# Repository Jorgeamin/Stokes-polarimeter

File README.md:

# Stokes-polarimeter
Supplement documents for article "Homemade open-source full-Stokes polarimeter based on division of amplitude"

* [python](python): This folder contains python scripts for user interface.\
    main application file **stokes_polarimeter.py**\
     -line 517:  ### Here your put the result of the calibration of the photodiodes ###\
     -line 526:  ### Here your put the result of the calibration to obtain the Stokes parameters ###
  
* [firmware](firmware): This folder contains MPLAB Harmony 3 firmware that should be installed in an ATSAML21E16B\
    file **main.c**\
	-line 97:  /// Here your put the result of the calibration of the photodiodes ///\
	-line 106: /// Here your put the result of the calibration to obtain the Stokes parameters ///
	
* [pcb](pcb): This folder contains the Autodesk Eagle electronic design files.
* [3d](3d): This folder contains the 3D Autodesk Inventor, STEP and STL files.
* [pdf](pdf): This folder contains the electronic diagrams and the 3D assembly in PDF format.

-this repository uses submodules

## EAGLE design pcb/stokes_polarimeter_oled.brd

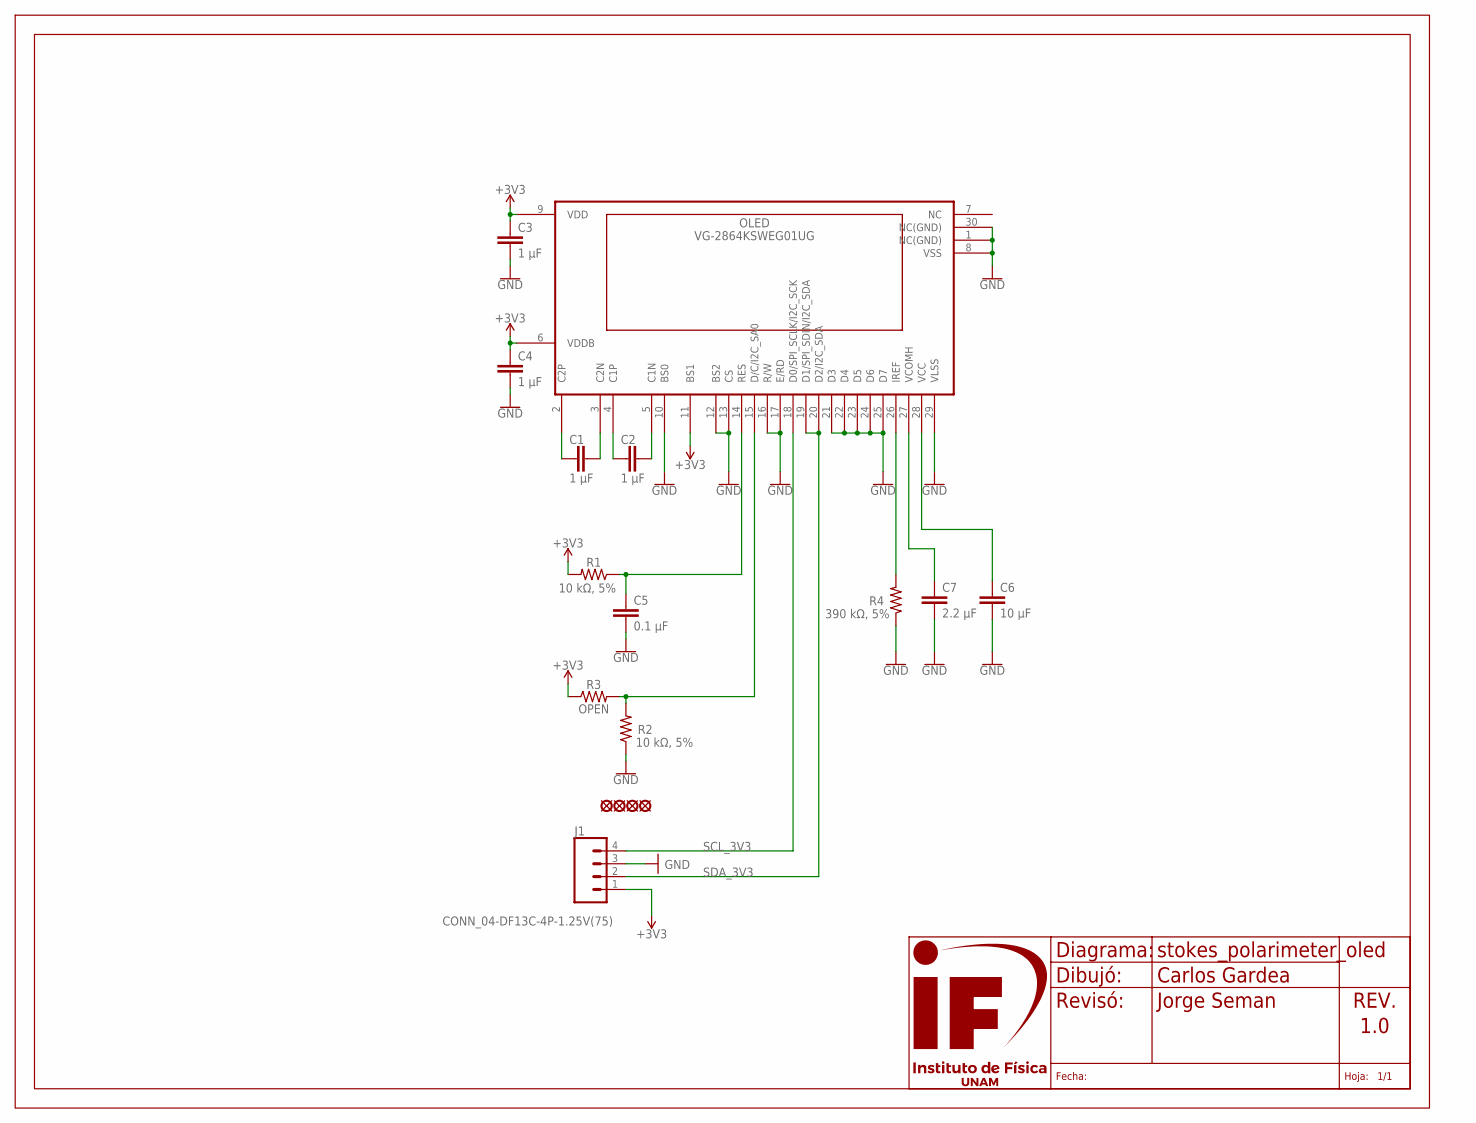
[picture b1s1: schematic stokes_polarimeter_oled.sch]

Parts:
C1, C2, C3, C4: 1 µF; C1206
C5: 0.1 µF; C1206
C6: 10 µF; C1206
C7: 2.2 µF; C1206
H5, H6, H7, H8: HOLE-M2.5; HOLE_2.5
J1: CONN_04-DF13C-4P-1.25V(75); DF13C4P125V
OLED: VG-2864KSWEG01UG; UG-2864HSWEG01
R1, R2: 10 kΩ, 5%; R1206
R3: OPEN; R1206_OPEN
R4: 390 kΩ, 5%; R1206
U$1: IFUNAM_FRAME_LETTER_HNONE; NONE

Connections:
+3V3: C3.1, C4.1, J1.1, OLED.6 (VDDB), OLED.9 (VDD), OLED.11 (BS1), R1.2, R3.1
GND: C3.2, C4.2, C5.2, C6.2, C7.2, J1.3, OLED.1 (NC(GND)), OLED.8 (VSS), OLED.10 (BS0), OLED.12 (BS2), OLED.13 (CS), OLED.16 (R/W), OLED.17 (E/RD), OLED.21 (D3), OLED.22 (D4), OLED.23 (D5), OLED.24 (D6), OLED.25 (D7), OLED.29 (VLSS), OLED.30 (NC(GND)), R2.1, R4.1
unnamed: C2.1, OLED.4 (C1P)
unnamed: C1.2, OLED.3 (C2N)
unnamed: C1.1, OLED.2 (C2P)
unnamed: C2.2, OLED.5 (C1N)
unnamed: C5.1, OLED.14 (RES), R1.1
unnamed: OLED.15 (D/C/I2C_SA0), R2.2, R3.2
unnamed: OLED.26 (IREF), R4.2
unnamed: C7.1, OLED.27 (VCOMH)
unnamed: C6.1, OLED.28 (VCC)
SCL_3V3: J1.4, OLED.18 (D0/SPI_SCLK/I2C_SCK)
SDA_3V3: J1.2, OLED.19 (D1/SPI_SDIN/I2C_SDA), OLED.20 (D2/I2C_SDA)

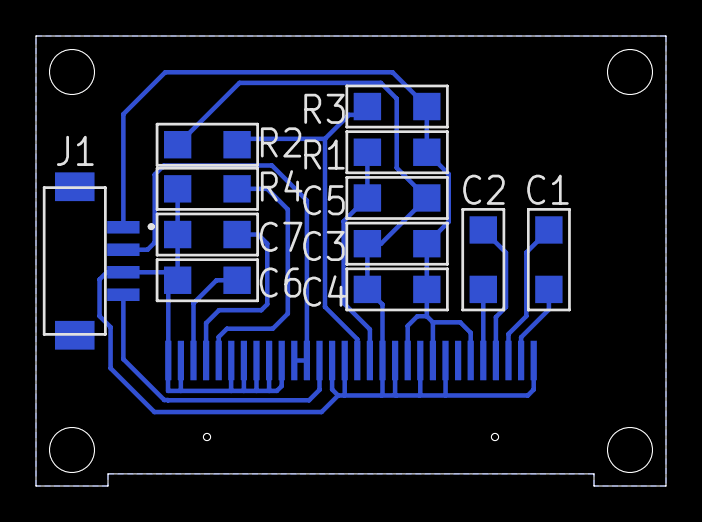
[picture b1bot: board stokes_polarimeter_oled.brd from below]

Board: 2 copper layers, 35.0 x 25.0 mm, 18 parts (12 on the bottom side), 13 nets.

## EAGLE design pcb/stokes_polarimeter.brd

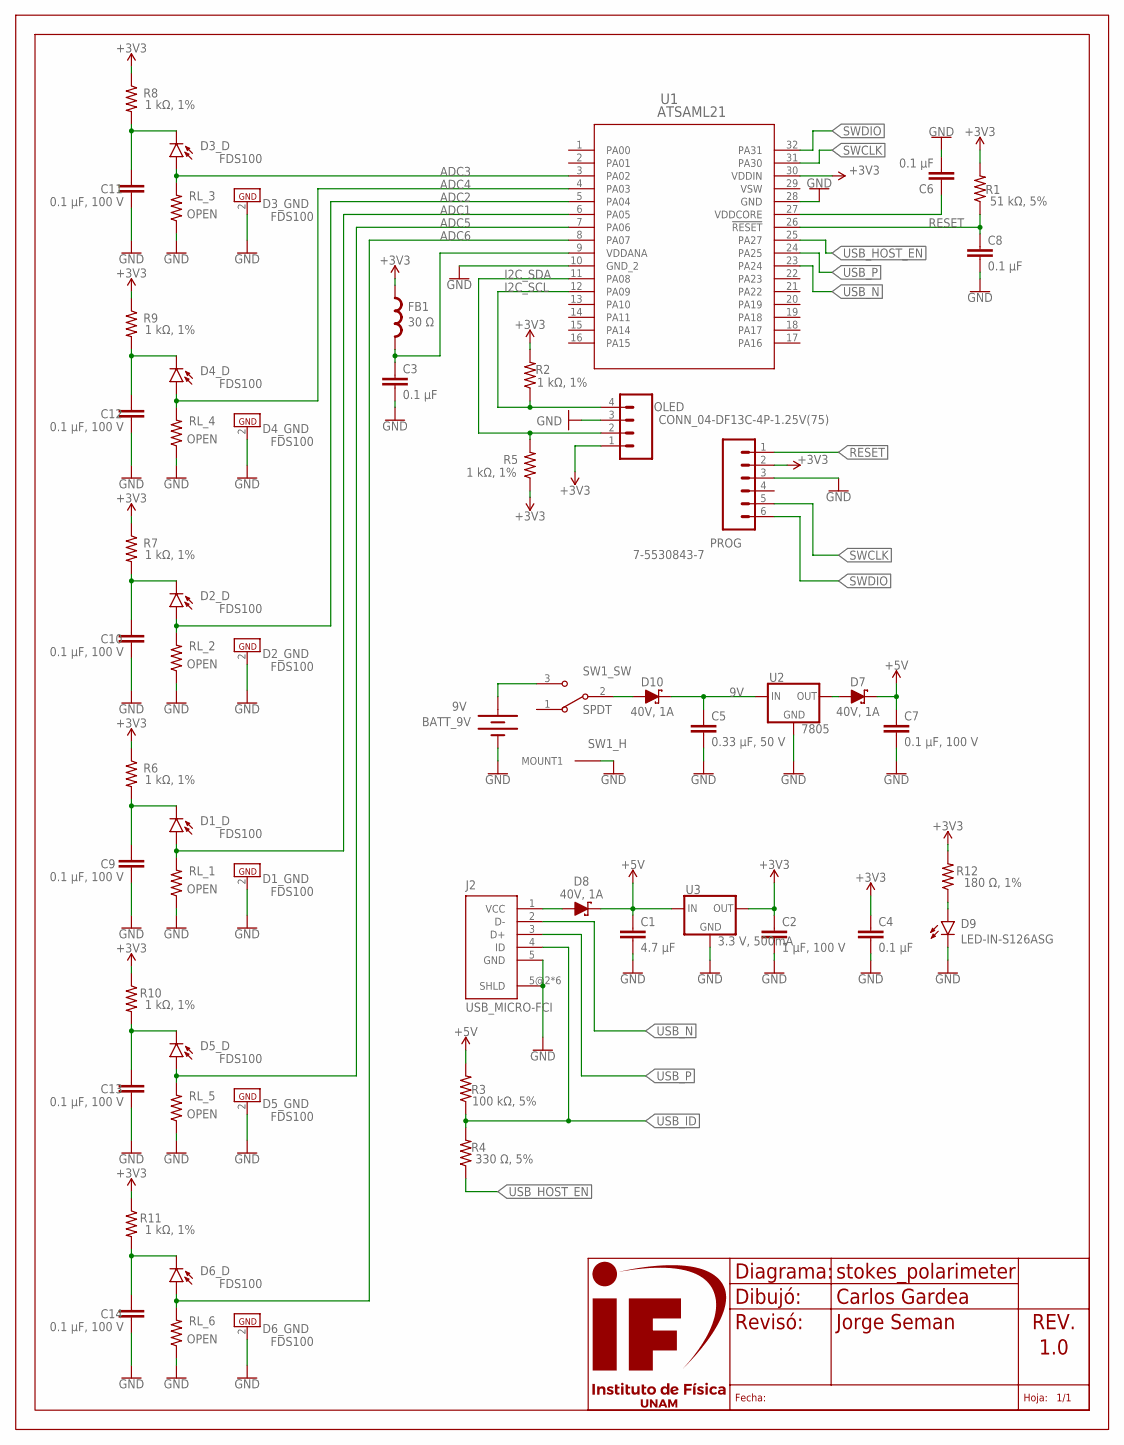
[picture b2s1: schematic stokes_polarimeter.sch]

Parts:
BATT_9V: 9V; 5331
C1: 4.7 µF; C1206
C2: 1 µF, 100 V; C1206
C3, C4, C6, C8: 0.1 µF; C1206
C5: 0.33 µF, 50 V; C1206
C7, C9, C10, C11, C12, C13, C14: 0.1 µF, 100 V; C1206
D1, D2, D3, D4, D5, D6: FDS100; FDS100_VERT
D7, D8, D10: 40V, 1A; DO-214AC
D9: LED-IN-S126ASG; IN-S126AS
FB1: 30 Ω; L1206
J2: USB_MICRO-FCI; 10103594-0001LF_FCI
OLED: CONN_04-DF13C-4P-1.25V(75); DF13C4P125V
PROG: 7-5530843-7
R1: 51 kΩ, 5%; R1206
R2, R5, R6, R7, R8, R9, R10, R11: 1 kΩ, 1%; R1206
R3: 100 kΩ, 5%; R1206
R4: 330 Ω, 5%; R1206
R12: 180 Ω, 1%; R1206
RL_1, RL_2, RL_3, RL_4, RL_5, RL_6: OPEN; R1206_OPEN
SW1: SPDT; SK12F17G7
U1: ATSAML21; TQFP32
U2: 7805; DPAK
U3: 3.3 V, 500mA; SOT223
U$54: IFUNAM_FRAME_LETTER_VNONE; NONE

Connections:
9V: C5.1, D10.K (C), U2.1 (IN)
+3V3: C2.1, C4.1, FB1.1, OLED.1, PROG.2, R1.2, R2.2, R5.1, R6.1, R7.1, R8.1, R9.1, R10.1, R11.1, R12.2, U1.30 (VDDIN), U3.3 (OUT)
+5V: C1.1, C7.1, D7.K (C), D8.K (C), R3.2, U3.1 (IN)
ADC1: D1.1 (A), RL_1.2, U1.6 (PA05)
ADC2: D2.1 (A), RL_2.2, U1.5 (PA04)
ADC3: D3.1 (A), RL_3.2, U1.3 (PA02)
ADC4: D4.1 (A), RL_4.2, U1.4 (PA03)
ADC5: D5.1 (A), RL_5.2, U1.7 (PA06)
ADC6: D6.1 (A), RL_6.2, U1.8 (PA07)
GND: BATT_9V.-, C1.2, C2.2, C3.2, C4.2, C5.2, C6.2, C7.2, C8.2, C9.2, C10.2, C11.2, C12.2, C13.2, C14.2, D1.2 (P$GND), D2.2 (P$GND), D3.2 (P$GND), D4.2 (P$GND), D5.2 (P$GND), D6.2 (P$GND), D9.K (C), J2.5 (GND), J2.5@2 (SHLD), J2.5@3 (SHLD), J2.5@4 (SHLD), J2.5@5 (SHLD), J2.5@6 (SHLD), J2.5@7 (SHLD), OLED.3, PROG.3, RL_1.1, RL_2.1, RL_3.1, RL_4.1, RL_5.1, RL_6.1, SW1.MH1 (MOUNT1), SW1.MH2 (MOUNT1), SW1.MH3 (MOUNT1), SW1.MH4 (MOUNT1), U1.10 (GND_2), U1.28 (GND), U2.4 (GND), U3.2 (GND), U3.4 (GND)
I2C_SCL: OLED.4, R2.1, U1.12 (PA09)
I2C_SDA: OLED.2, R5.2, U1.11 (PA08)
unnamed: C10.1, D2.3 (C), R7.2
unnamed: D10.A, SW1.2 (COMMON)
unnamed: C9.1, D1.3 (C), R6.2
unnamed: D9.A, R12.1
unnamed: C11.1, D3.3 (C), R8.2
unnamed: BATT_9V.+, SW1.3 (NO)
unnamed: C12.1, D4.3 (C), R9.2
unnamed: C13.1, D5.3 (C), R10.2
unnamed: C14.1, D6.3 (C), R11.2
unnamed: D7.A, U2.3 (OUT)
unnamed: D8.A, J2.1 (VCC)
RESET: C8.1, PROG.1, R1.1, U1.26 (!RESET)
SWCLK: PROG.5, U1.31 (PA30)
SWDIO: PROG.6, U1.32 (PA31)
USB_HOST_EN: R4.1, U1.25 (PA27)
USB_ID: J2.4 (ID), R3.1, R4.2
USB_N: J2.2 (D-), U1.23 (PA24)
USB_P: J2.3 (D+), U1.24 (PA25)
VDDANA: C3.1, FB1.2, U1.9 (VDDANA)
VDDCORE: C6.1, U1.27 (VDDCORE)

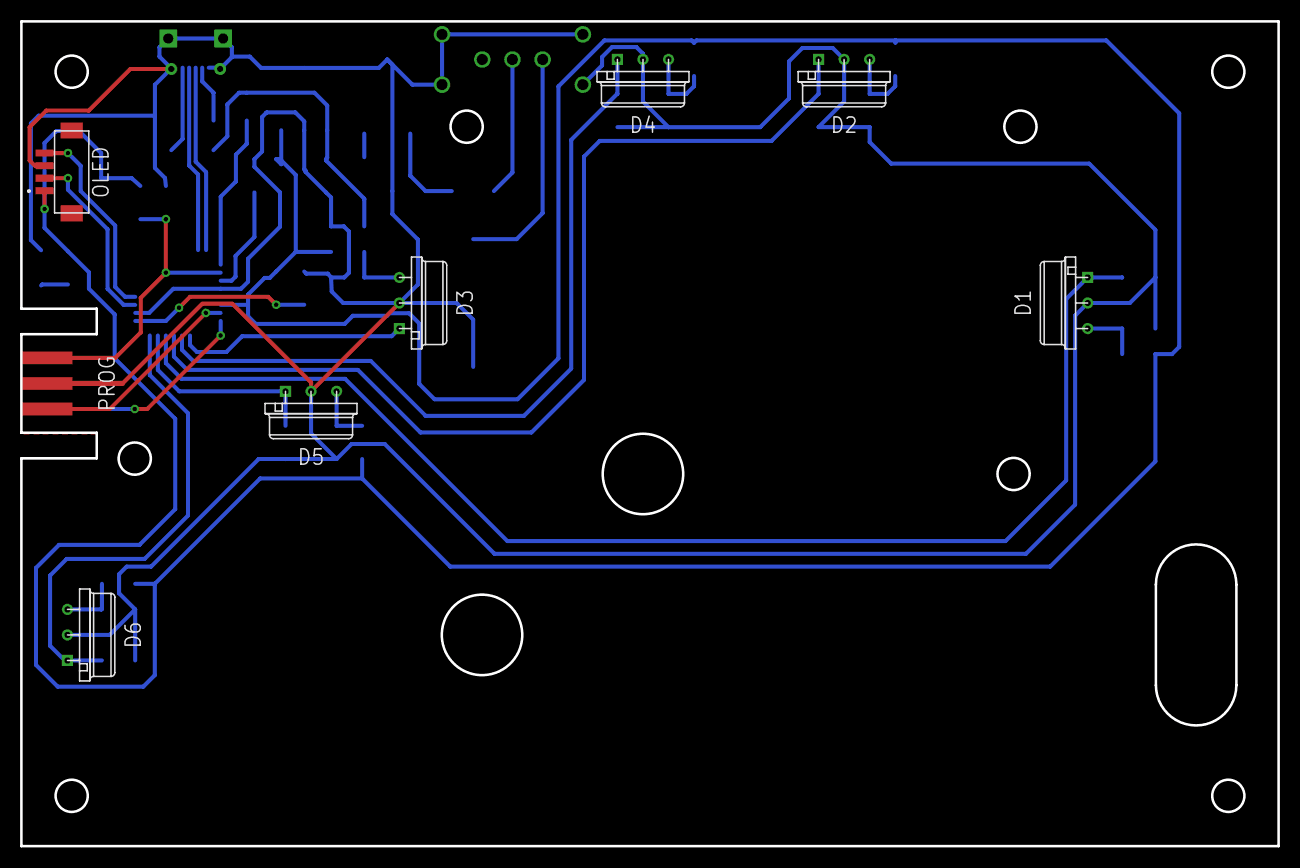
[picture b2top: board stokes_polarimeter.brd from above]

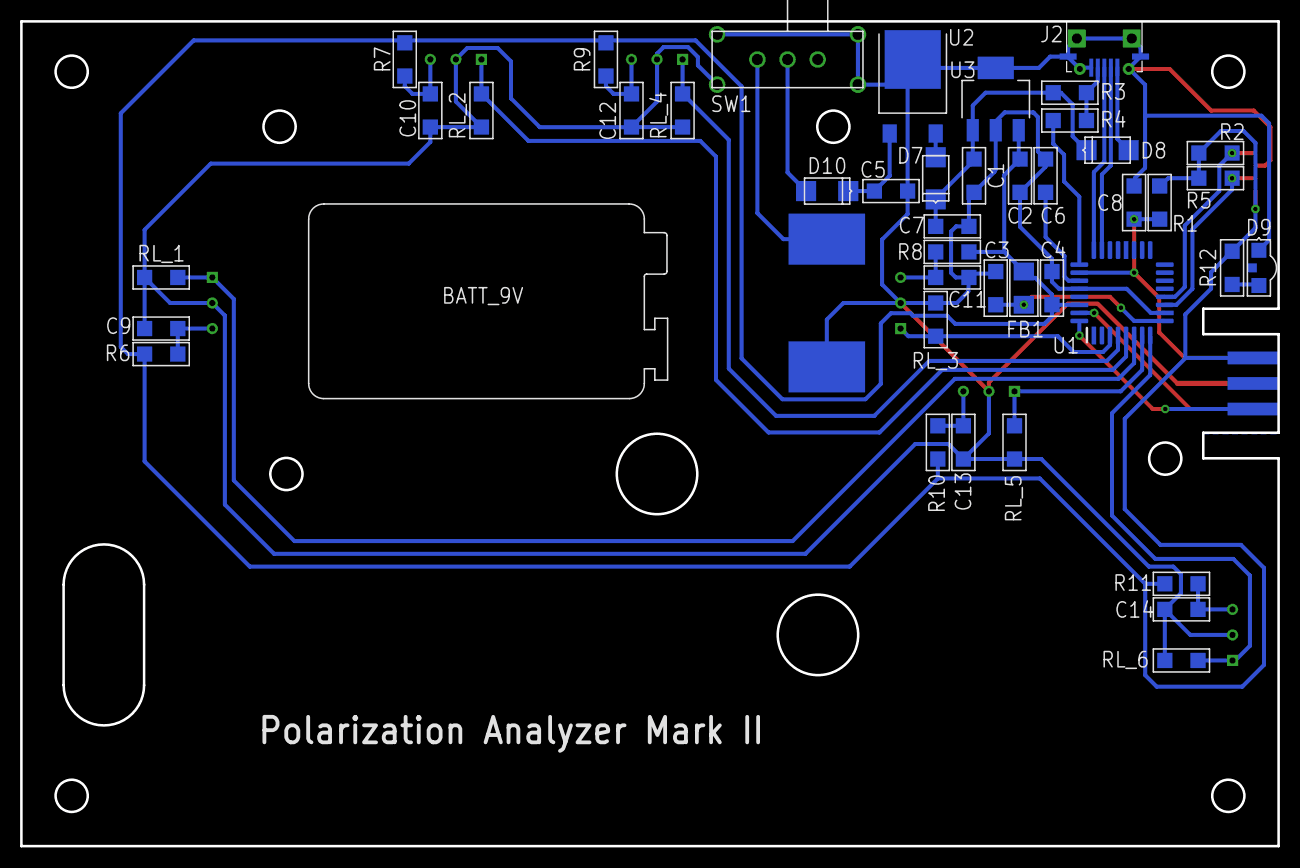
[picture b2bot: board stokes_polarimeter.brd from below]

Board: 2 copper layers, 125.0 x 82.0 mm, 52 parts (43 on the bottom side), 32 nets.

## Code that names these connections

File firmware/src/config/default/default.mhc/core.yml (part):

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    - type: Values
      children:
      - type: Dynamic
        attributes: {id: core, value: PA02}
  - type: String
    attributes: {id: PORT_GROUP_0_PAD_22}
    children:
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    - type: Values
      children:
      - type: Dynamic
        attributes: {id: core, value: PA24}
  - type: String
    attributes: {id: PORT_GROUP_0_PAD_25}
    children:
    - type: Values
      children:
      - type: Dynamic
        attributes: {id: core, value: PA25}
  - type: String
    attributes: {id: PORT_GROUP_0_PAD_27}
    children:
    - type: Values
      children:
      - type: Dynamic
        attributes: {id: core, value: PA27}
  - type: String
    attributes: {id: PORT_GROUP_0_PAD_3}
    children:
    - type: Values
      children:
      - type: Dynamic
        attributes: {id: core, value: PA03}
  - type: String
    attributes: {id: PORT_GROUP_0_PAD_4}
    children:
    - type: Values
      children:
      - type: Dynamic
        attributes: {id: core, value: PA04}
  - type: String
    attributes: {id: PORT_GROUP_0_PAD_5}
    children:
    - type: Values
      children:
      - type: Dynamic
        attributes: {id: core, value: PA05}
  - type: String
    attributes: {id: PORT_GROUP_0_PAD_6}
    children:
    - type: Values
      children:
      - type: Dynamic
        attributes: {id: core, value: PA06}
  - type: String
    attributes: {id: PORT_GROUP_0_PAD_7}
    children:
    - type: Values
      children:
      - type: Dynamic
        attributes: {id: core, value: PA07}
  - type: String
    attributes: {id: PORT_GROUP_0_PAD_8}
    children:
    - type: Values
      children:
      - type: Dynamic
        attributes: {id: core, value: PA08}
  - type: String
    attributes: {id: PORT_GROUP_0_PAD_9}
    children:
    - type: Values
      children:
      - type: Dynamic
        attributes: {id: core, value: PA09}
  - type: String
    attributes: {id: PORT_GROUP_0_PINCFG11}
    children:
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
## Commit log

2024-04-06 adding submodules
2024-05-09 adding citation file
2024-06-18 Update CITATION.cff
    We updated the citation file including the DOI from Optica Open.
2024-06-18 We added the orcid number of one author.
